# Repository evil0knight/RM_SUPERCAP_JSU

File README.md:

# RM 超级电容控制器

本仓库整合了我的两个 RoboMaster 超级电容控制器项目。

| 项目               | 来源             | 主控      | 目录                                      |
| ------------------ | ---------------- | --------- | ----------------------------------------- |
| RM_SUPERCAP_JSU    | 复刻桂林理工大学 | STM32G431 | [`gui_lin_li_gong/`](./gui_lin_li_gong/)   |
| RM_SUPERCAP_JSU_V2 | 复刻香港科技大学 | STM32F334 | [`xiang_gang_ke_ji/`](./xiang_gang_ke_ji/) |

---

## 一、RM_SUPERCAP_JSU（复刻桂林理工大学）

复刻 RM 桂林理工大学的开源
我们学校一直没有超电，或许我能填补这个空缺

**10.8**
已经做出来了，上车测试功能完好，能充电能放电，暂时没有遇到问题

**10.19**

---

## 二、RM_SUPERCAP_JSU_V2（复刻香港科技大学）

复刻香港科技大学

**11.1**
现在的问题是电容端口短路，初步怀疑是原件选型错误，解决方法：加上了群里的同学一起讨论，和队里的研究生一起排查，看研究生的学习笔记，学习 C++

**11.13**
GAME WILL OVER，lucky，终于冲放电成功了，不报错，不过另一个的上板电流采样芯片可能坏了，等快递

**11.15**
研究生学姐走了，剩下的成果归本人所有

**11.18**
第二个也做出来了，一开始错误的原因是底盘电流检测芯片选型错误，要 INA240PW1 才是对的，INA240PW2 的增益是不同的
这如此种种也不过如此啊

**11.19**
炸了....

**11.20**
上车正常，最终效果：可以成功存储能量，要用的时候再输出，根据功率自动选择存储还是释放，功率闭环 + 缓冲能量闭环

## 2026/4/28

我准备拿香港科技大学的硬件基础,重新写一遍程序,因为他里面有些地方有问题,很多人都是看不懂他们的代码,他们拿C++写的,就是为了炫技,同学们看不懂代码确实不好调,我拿C语言重新写一遍,不过这个项目要在打完所有比赛再开始,也算是我人生中为大学里的竞赛留下最后一点痕迹

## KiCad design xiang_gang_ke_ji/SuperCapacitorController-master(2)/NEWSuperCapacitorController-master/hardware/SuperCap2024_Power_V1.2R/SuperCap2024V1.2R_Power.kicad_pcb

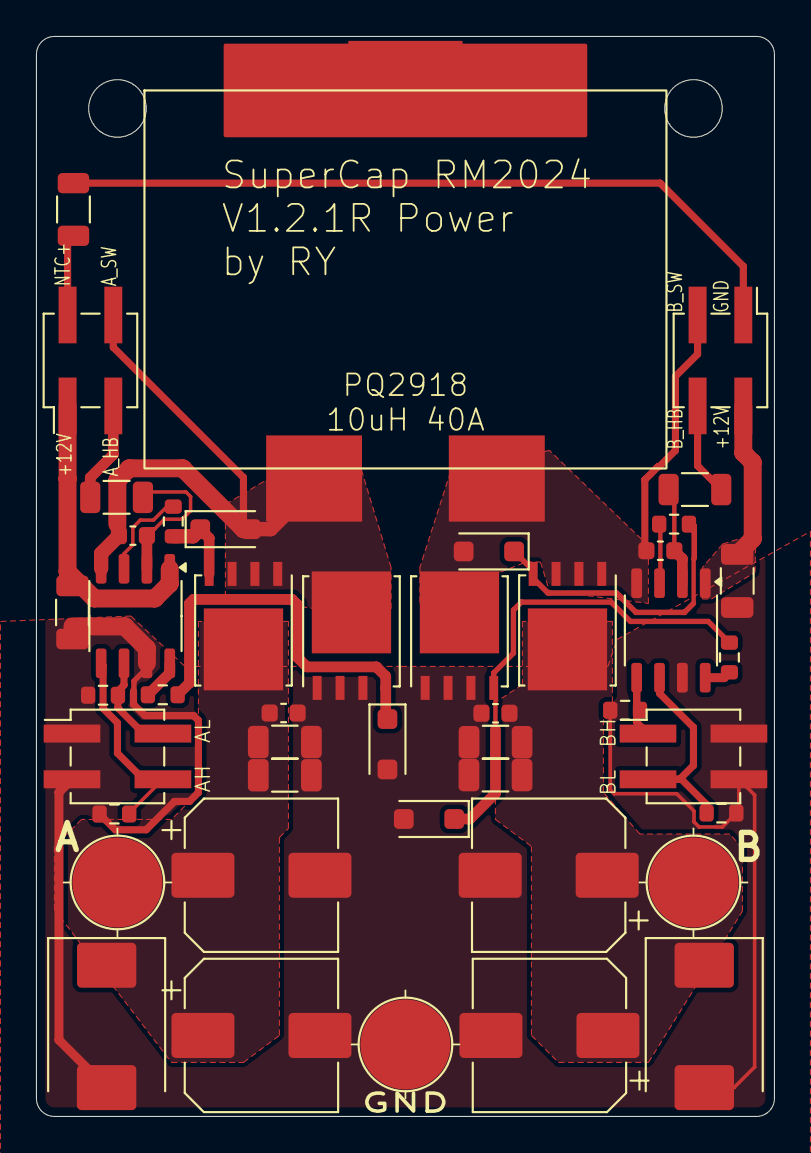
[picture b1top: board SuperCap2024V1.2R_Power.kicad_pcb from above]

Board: 2 copper layers, 41.0 x 60.0 mm, 47 parts (0 on the bottom side), 24 nets.

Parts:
C1, C13: 10u; C_0603_1608Metric
C2, C3, C5, C6: 220u; CP_Elec_8x10
C4, C9, C10, C11, C12, C14: 10u; C_1206_3216Metric
C7, C8: 100n; C_0603_1608Metric
D1, D2: TVS; D_SMC
D3, D4, D5, D6: SMF10A; D_SOD-123F
H1: GND; TestPoint_Pad_D4.0mm
H2, H5: MountingHole; MountingHole_3.2mm_M3
H3: A; TestPoint_Pad_D4.0mm
H4: B; TestPoint_Pad_D4.0mm
J1, J2, J3, J4: Conn_02x02_Odd_Even; PinHeader_2x02_P2.54mm_Vertical_SMD
L1: 10u 40A; PQ2617BHA
Q1, Q2, Q3, Q4: BSC070N10NS3G; TDSON-8-1_HandSolder
R1, R2: 120r; R_1206_3216Metric
R3, R4, R5, R6: 3.3r; R_0603_1608Metric
R7, R8, R9, R10: 10k; R_0603_1608Metric
TH1: 10k NTC; R_1206_3216Metric
U1, U2: UCC27201ADR; SOP-8_3.9x4.9mm_P1.27mm

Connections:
+12V: C4.1, C14.1, J1.1, J2.2, U1.1 (VDD), U2.1 (VDD)
/A_HB: J1.3, R1.2
/A_HG: D3.1 (A1), Q1.4 (G), R3.2
/A_HI: J3.4, R8.1, U1.5 (HI)
/A_LG: D5.1 (A1), Q3.4 (G), R4.2
/A_LI: J3.2, R7.1, U1.6 (LI)
/A_SW: C1.2, D3.2 (A2), J1.4, L1.1, Q1.1 (S), Q1.2 (S), Q1.3 (S), Q3.5 (D), U1.4 (HS)
/B_HB: J2.4, R2.2
/B_HG: D4.1 (A1), Q2.4 (G), R5.2
/B_HI: J4.1, R9.1, U2.5 (HI)
/B_LG: D6.1 (A1), Q4.4 (G), R6.2
/B_LI: J4.3, R10.1, U2.6 (LI)
/B_SW: C13.2, D4.2 (A2), J2.3, L1.2, Q2.1 (S), Q2.2 (S), Q2.3 (S), Q4.5 (D), U2.4 (HS)
A_POWER: C2.1, C5.1, C7.2, C9.2, C11.2, D1.1 (K), H3.1, Q1.5 (D)
B_POWER: C3.1, C6.1, C8.2, C10.2, C12.2, D2.1 (K), H4.1, Q2.5 (D)
GND: C2.2, C3.2, C4.2, C5.2, C6.2, C7.1, C8.1, C9.1, C10.1, C11.1, C12.1, C14.2, D1.2 (A), D2.2 (A), D5.2 (A2), D6.2 (A2), H1.1, J3.1, J3.3, J4.2, J4.4, Q3.1 (S), Q3.2 (S), Q3.3 (S), Q4.1 (S), Q4.2 (S), Q4.3 (S), R7.2, R8.2, R9.2, R10.2, U1.7 (VSS), U2.7 (VSS)
GND2: J2.1, TH1.2
NTC: J1.2, TH1.1
unnamed: C1.1, R1.1, U1.2 (HB)
unnamed: R3.1, U1.3 (HO)
unnamed: R4.1, U1.8 (LO)
unnamed: C13.1, R2.1, U2.2 (HB)
unnamed: R5.1, U2.3 (HO)
unnamed: R6.1, U2.8 (LO)

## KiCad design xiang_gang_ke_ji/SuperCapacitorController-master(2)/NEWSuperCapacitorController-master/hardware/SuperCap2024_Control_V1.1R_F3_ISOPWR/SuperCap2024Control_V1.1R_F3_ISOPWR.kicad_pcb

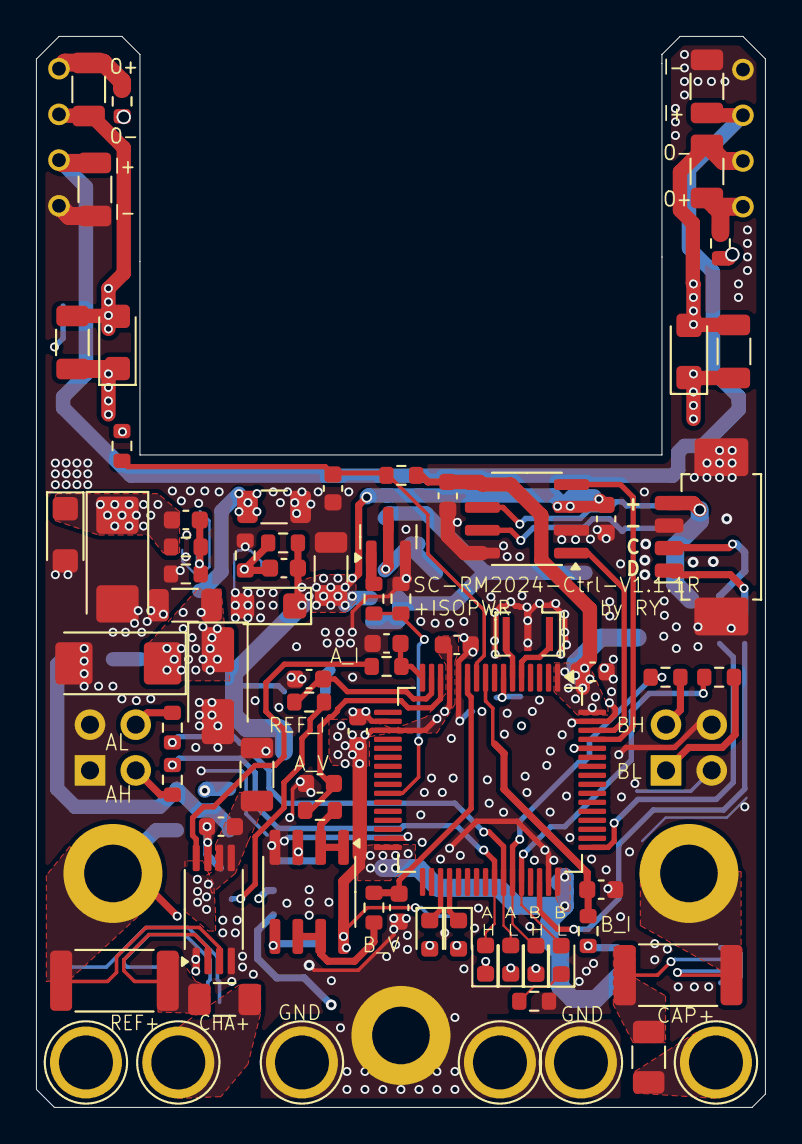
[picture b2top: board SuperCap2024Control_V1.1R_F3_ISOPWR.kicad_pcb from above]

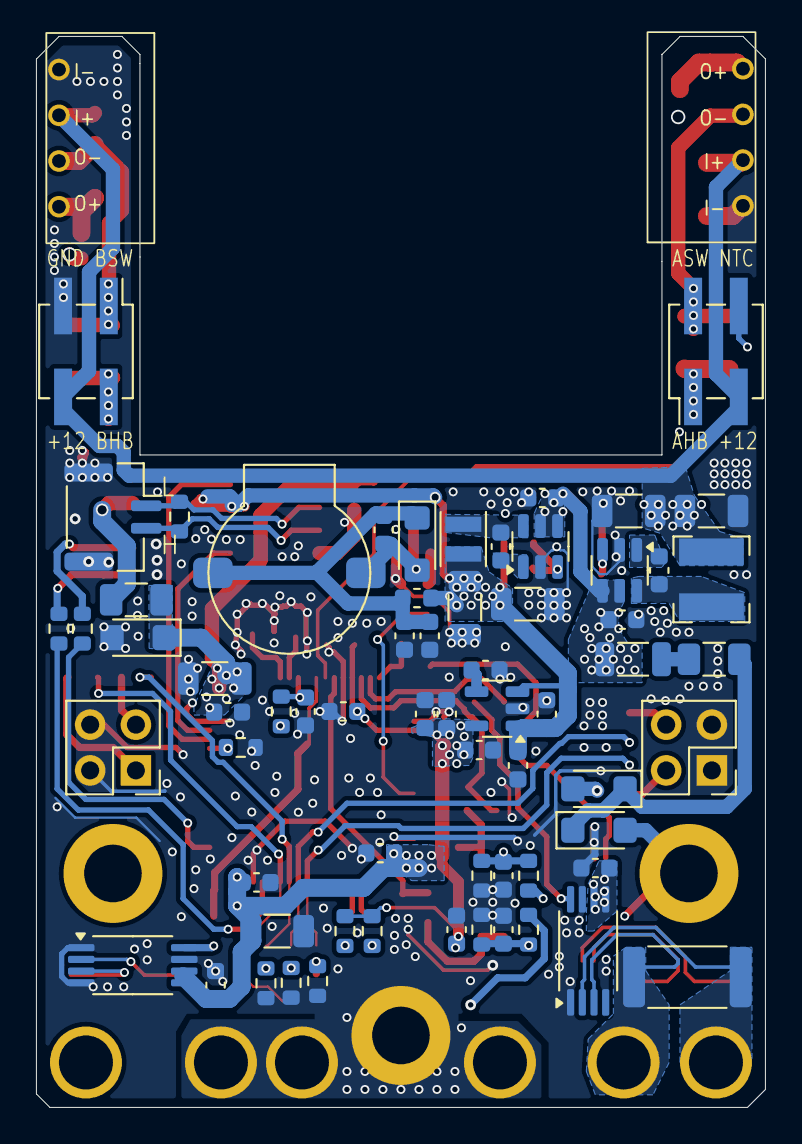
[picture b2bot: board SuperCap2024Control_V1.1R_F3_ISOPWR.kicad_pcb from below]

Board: 4 copper layers, 40.5 x 59.5 mm, 144 parts (67 on the bottom side), 74 nets.

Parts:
BZ1: Buzzer-9032; MLT-9032
C1, C8, C10, C11, C12, C13, C14, C17, C19, C20, C21, C22, C23, C24, C25, C26, C27, C28, C29, C30, C31, C32, C33, C39, C41, C47: 100n; C_0603_1608Metric
C3, C5, C15, C16, C34, C40, C42: 10u; C_0603_1608Metric
C4: 20p; C_0603_1608Metric
C9, C18, C36, C37, C44, C45, C49, C50, C52, C53, C54, C55: 10u; C_1206_3216Metric
C35, C48: 100p; C_0603_1608Metric
C38, C46: C_Polarized; CP_EIA-6032-28_Kemet-C
C43: 10n; C_0603_1608Metric
C51, C56, C57, C58: 100u 6.3V; C_1206_3216Metric
D1, D2, D3: DSS34; D_SMF
D4: SMF3.3A; D_SMF
D5: SMAJ28A; D_SMA
D6, D7, D8, D9, D13, D14: LED; LED_0603_1608Metric
D10, D11, D19: SMF10A; D_SMF
D22: SMF5V0A; D_SMF
F1, F2: 30A; Fuse_1206_3216Metric
F3, F4: 1A; Fuse_1206_3216Metric
FB1: FerriteBead; L_1206_3216Metric
FB2: FerriteBead; L_0603_1608Metric
H1, H2, H3: MountingHole_Pad; MountingHole_3.2mm_M3_ISO14580_Pad
J1, J4: Conn_02x02_Odd_Even; PinHeader_2x02_P2.54mm_Vertical_SMD
J2: Conn_01x02_MountingPin; JST_GH_SM02B-GHS-TB_1x02-1MP_P1.25mm_Horizontal
J3: Conn_01x04_MountingPin; Molex_PicoBlade_53261-0471_1x04-1MP_P1.25mm_Horizontal
J5, J6: Conn_02x02_Odd_Even; PinHeader_2x02_P2.54mm_Vertical
L1: 4.7u; L_Bourns-SRN4018
L2: 4.7u; L_Sunlord_SWPA252012S
Q1: AO3400A; SOT-23
R1, R2, R3, R4, R5, R22, R23, R24, R26, R27, R37: 33r; R_0603_1608Metric
R6, R28, R40, R42: 10k; R_0603_1608Metric
R7, R8, R10, R11: 2.2k; R_0603_1608Metric
R9, R12, R15: 2mr; R_2512_6332Metric
R13, R14, R30, R31: 1k; R_0603_1608Metric
R16, R19: 90k 25ppm; R_0603_1608Metric
R17, R20: 10k 25ppm; R_0603_1608Metric
R18, R21: 68r; R_0603_1608Metric
R25, R36, R38: 120r; R_0603_1608Metric
R39: 118k; R_0603_1608Metric
R41: 53.6k; R_0603_1608Metric
TP1, TP2, TP3, TP4, TP5, TP6: TestPoint; TestPoint_Plated_Hole_D3.0mm
U1, U3: ISO_DC; BxxxxS-1W
U2, U4, U5: INA240A1PW; TSSOP-8_4.4x3mm_P0.65mm
U6: GS8332-SR; SOIC-8_3.9x4.9mm_P1.27mm
U7: STM32F334R8Tx; LQFP-64_10x10mm_P0.5mm
U8: SIT1042/3; SOIC-8_3.9x4.9mm_P1.27mm
U9, U11: RY8411; SOT-23-6
U10: RS3236; SOT-23-5
Y1: CSTCE8M; Resonator_SMD_Murata_CSTxExxV-3Pin_3.0x1.1mm

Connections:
+3.3V: C10.1, C11.1, C12.1, C13.1, C14.1, C15.1, C16.2, C17.2, C19.1, C21.1, C22.1, C27.2, C40.1, C41.1, C42.1, C56.1, C57.1, C58.1, D4.1 (A1), F3.1, R13.1, R28.1, R30.2, R31.2, U2.5 (V+), U2.6 (REF2), U4.5 (V+), U4.6 (REF2), U5.5 (V+), U5.6 (REF2), U6.8 (VDD), U7.1 (VBAT), U7.13 (VDDA), U7.19 (VDD), U7.32 (VDD), U7.48 (VDD), U7.64 (VDD), U8.5 (VIO), U10.5 (OUT)
+5V: C26.2, C34.1, C39.1, C48.1, C49.1, C50.1, C51.1, D22.1 (A1), FB2.1, L2.2, R41.1, U8.3 (VCC), U10.1 (IN), U10.3 (EN)
+12V: C35.1, C36.1, C37.1, C38.1, C54.2, C55.2, D19.1 (A1), J1.4, J4.3, L1.2, R39.1, U1.2 (VIN+), U3.2 (VIN+)
/A_H: D6.2 (A), R1.1, U7.41 (PA8)
/A_L: D7.2 (A), R2.1, U7.42 (PA9)
/B_H: D8.2 (A), R3.1, U7.43 (PA10)
/B_L: D9.2 (A), R4.1, U7.44 (PA11)
A_HB: C18.2, D10.1 (A1), J4.1, R18.2
A_H_OUT: J6.2, R1.2
A_I: R23.1, U4.8
A_I_ADC: C28.2, R23.2, U7.16 (PA2)
A_L_OUT: J6.4, R2.2
A_POWER: D1.2 (A), H1.1, R12.2, R16.1, U4.3 (-)
A_SW: C9.1, C18.1, D10.2 (A2), J4.2, U1.3 (VOUT-)
BUZZER: R5.1, R6.2, U7.26 (PB0)
B_HB: C53.2, D11.1 (A1), J1.2, R21.2
B_H_OUT: J5.3, R3.2
B_L_OUT: J5.1, R4.2
B_POWER: D2.2 (A), H2.1, R15.1, R19.1, U5.3 (-)
B_SW: C52.1, C53.1, D11.2 (A2), J1.1, U3.3 (VOUT-)
CANH: J2.2, R25.2, U8.7 (CANH)
CANL: J2.1, R25.1, U8.6 (CANL)
CAN_RX: U7.61 (PB8), U8.4 (RXD)
CAN_TX: U7.62 (PB9), U8.1 (TXD)
CAP+: F2.2, TP5.1
CAP_I: R24.1, U5.8
CAP_I_ADC: C29.2, R24.2, U7.9 (PC1)
CHASSIS+: F1.1, R9.2, TP3.1, U2.3 (-)
GND: C1.1, C3.1, C5.1, C8.2, C10.2, C11.2, C12.2, C13.2, C14.2, C15.2, C16.1, C17.1, C19.2, C20.2, C21.2, C22.2, C23.2, C24.2, C25.1, C26.1, C27.1, C28.1, C29.1, C30.1, C31.1, C32.2, C34.2, C36.2, C37.2, C38.2, C39.2, C40.2, C41.2, C42.2, C43.2, C44.2, C45.2, C46.2, C49.2, C50.2, C51.2, C54.1, C55.1, C56.2, C57.2, C58.2, D4.2 (A2), D5.2 (A2), D19.2 (A2), D22.2 (A2), H3.1, J1.3, J2.MP (MountPin), J3.3, J3.MP (MountPin), J5.2, J5.4, J6.1, J6.3, Q1.2 (S), R6.1, R7.1, R8.1, R10.1, R11.1, R14.1, R17.1, R20.1, R40.2, R42.2, TP2.1, TP4.1, TP6.1, U1.1 (VIN-), U2.1 (GND), U2.4 (GND), U2.7 (REF1), U3.1 (VIN-), U4.1 (GND), U4.4 (GND), U4.7 (REF1), U5.1 (GND), U5.4 (GND), U5.7 (REF1), U6.4 (VSS), U7.12 (VSSA), U7.18 (VSS), U7.31 (VSS), U7.47 (VSS), U7.63 (VSS), U8.2 (GND), U8.8 (STB), U9.2 (GND), U10.2 (GND), U11.2 (GND), Y1.2
IA+: F1.2, R12.1, U4.2 (+)
IB+: F2.1, R15.2, U5.2 (+)
NTC: J4.4, R37.1
unnamed: BZ1.2 (+), C3.2, C4.2, C5.2, D3.1 (K), FB2.2
unnamed: BZ1.1 (-), C4.1, D3.2 (A), Q1.3 (D)
unnamed: C23.1, R16.2, R17.2, U6.3 (+)
unnamed: C24.1, R19.2, R20.2, U6.5 (+)
unnamed: D1.1 (K), D2.1 (K), F4.1
unnamed: D6.1 (K), R7.2
unnamed: D7.1 (K), R8.2
unnamed: D8.1 (K), R10.2
unnamed: D9.1 (K), R11.2
unnamed: D13.2 (A), R30.1
unnamed: D14.2 (A), R31.1
unnamed: F4.2, FB1.1
unnamed: J3.1, R38.2
unnamed: J3.2, R36.2
unnamed: F3.2, J3.4
unnamed: Q1.1 (G), R5.2
unnamed: C9.2, R18.1, U1.4 (VOUT+)
unnamed: C52.2, R21.1, U3.4 (VOUT+)
unnamed: R14.2, U7.60 (BOOT0)
unnamed: C20.1, R13.2, U7.7 (NRST)
unnamed: U7.5 (PF0), Y1.1
unnamed: U7.6 (PF1), Y1.3
unnamed: C33.1, U9.1 (BS)
unnamed: C35.2, R39.2, R40.1, U9.3 (FB)
unnamed: C33.2, L1.1, U9.6 (LX)
unnamed: C43.1, U10.4 (BP/FB)
unnamed: C47.1, U11.1 (BS)
unnamed: C48.2, R41.2, R42.1, U11.3 (FB)
unnamed: C47.2, L2.1, U11.6 (LX)
PB14: D14.1 (K), U7.35 (PB14)
PB15: D13.1 (K), U7.36 (PB15)
REFEREE+: R9.1, TP1.1, U2.2 (+)
REFEREE_I: R22.1, U2.8
REFEREE_I_ADC: C25.2, R22.2, U7.15 (PA1)
SWDCK: R36.1, U7.49 (PA14)
SWDIO: R38.1, U7.46 (PA13)
Thermistor_ADC: C32.1, R28.2, R37.2, U7.10 (PC2)
VASENSE: R26.1, U6.1 (OUTA), U6.2 (-)
VASENSE_ADC: C30.2, R26.2, U7.14 (PA0)
VBSENSE: R27.1, U6.6 (-), U6.7 (OUTB)
VBSENSE_ADC: C31.2, R27.2, U7.11 (PC3)
VPP: C1.2, C8.1, C44.1, C45.1, C46.1, D5.1 (A1), FB1.2, U9.4 (EN), U9.5 (IN), U11.4 (EN), U11.5 (IN)

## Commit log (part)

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2025-10-03 Initial plan
2025-10-03 Revert "[WIP] 构建一个文件夹用来放照片,再来一个文件夹放代码,再来一个文件夹放PCB,再来一个放相关资料,最后一个放STEP文件,本工程私人用,未来用于面试"
2025-10-03 Add explanation for understanding function logic
2025-10-03 Update project focus description in README
2026-03-28 Add README images
2026-03-29 Update README and add images
2026-04-28 Add new files and update tutorial
    - Update 超电傻瓜式使用教程.md
    - Add 修改内容.md
    - Add SuperCapacitorController-master(2) project files
    - Add image assets
    - Add super_cap_extract_20260428
2026-04-28 Add hardware files, STEP model, PDF report, and boom assets
